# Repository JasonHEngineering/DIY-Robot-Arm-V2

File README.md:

## DIY Robot Arm V2
This repository is for archiving a prior 6 DOF robot project that is no longer maintained.
I am now working on the next V3 version instead. 

### Contents
| Folder  | Contents|
| ------------- | ------------- |
| [Adaptor Board](https://github.com/JasonHEngineering/DIY-Robot-Arm-V2/tree/main/Adaptor%20Board%20(schema%2C%20gerbers%2C%20kicad%20project%20folder)) | KiCad Project files. Gerber files for PCB. But no SMD assembly because for this variant of adaptor board, I did the soldering myself using both soldering iron and hot air solder. |
| [Arduino Nano](https://github.com/JasonHEngineering/DIY-Robot-Arm-V2/tree/main/Arduino%20Nano%20(.ino%20file)) | Load this file into Arduino Nano 33 BLE/IoT device. This is to be mounted into adaptor board above. |
| [CAD files](https://github.com/JasonHEngineering/DIY-Robot-Arm-V2/tree/main/CAD%20files%20(2d%2C%20step)) | Step files and 2d drawings. 2d drawings are not fully detailed; mainly the threads and tight tolerances are detailed. |
| [Raspberry Pi](https://github.com/JasonHEngineering/DIY-Robot-Arm-V2/tree/main/Raspberry%20Pi%20(plotly%20dash%20host)) | Python script and dependencies to be run on raspberry Pi 3/4 |

### Mechanical Structure
Machined CNC parts placement in assembly as shown below. 
> [!NOTE]
> In such a setup, micro limit switches can only zero the respective axis angles approximately. Next version shall use absolute encoders.    

Below illustration of user interface dealing with forward kinematics values:  

### Inverse Kinematics Solver
[Python solver](https://github.com/JasonHEngineering/Inverse-Kinematics)
1. Inverse Kinematics (CCD) – Cyclic Coordinate Descent in 3d space
2. Inverse Kinematics (vector formula Jacobian) - Euler
3. Inverse Kinematics (Numerical Jacobian) - Euler
4. Inverse Kinematics (Numerical Jacobian) - Quaternion

### Quick Illustration at YouTube

### Additional Info at WordPress
For more data/info, please refer to this [WordPress page](https://jashuang1983.wordpress.com/robotics-6-dof-arm-v2/).

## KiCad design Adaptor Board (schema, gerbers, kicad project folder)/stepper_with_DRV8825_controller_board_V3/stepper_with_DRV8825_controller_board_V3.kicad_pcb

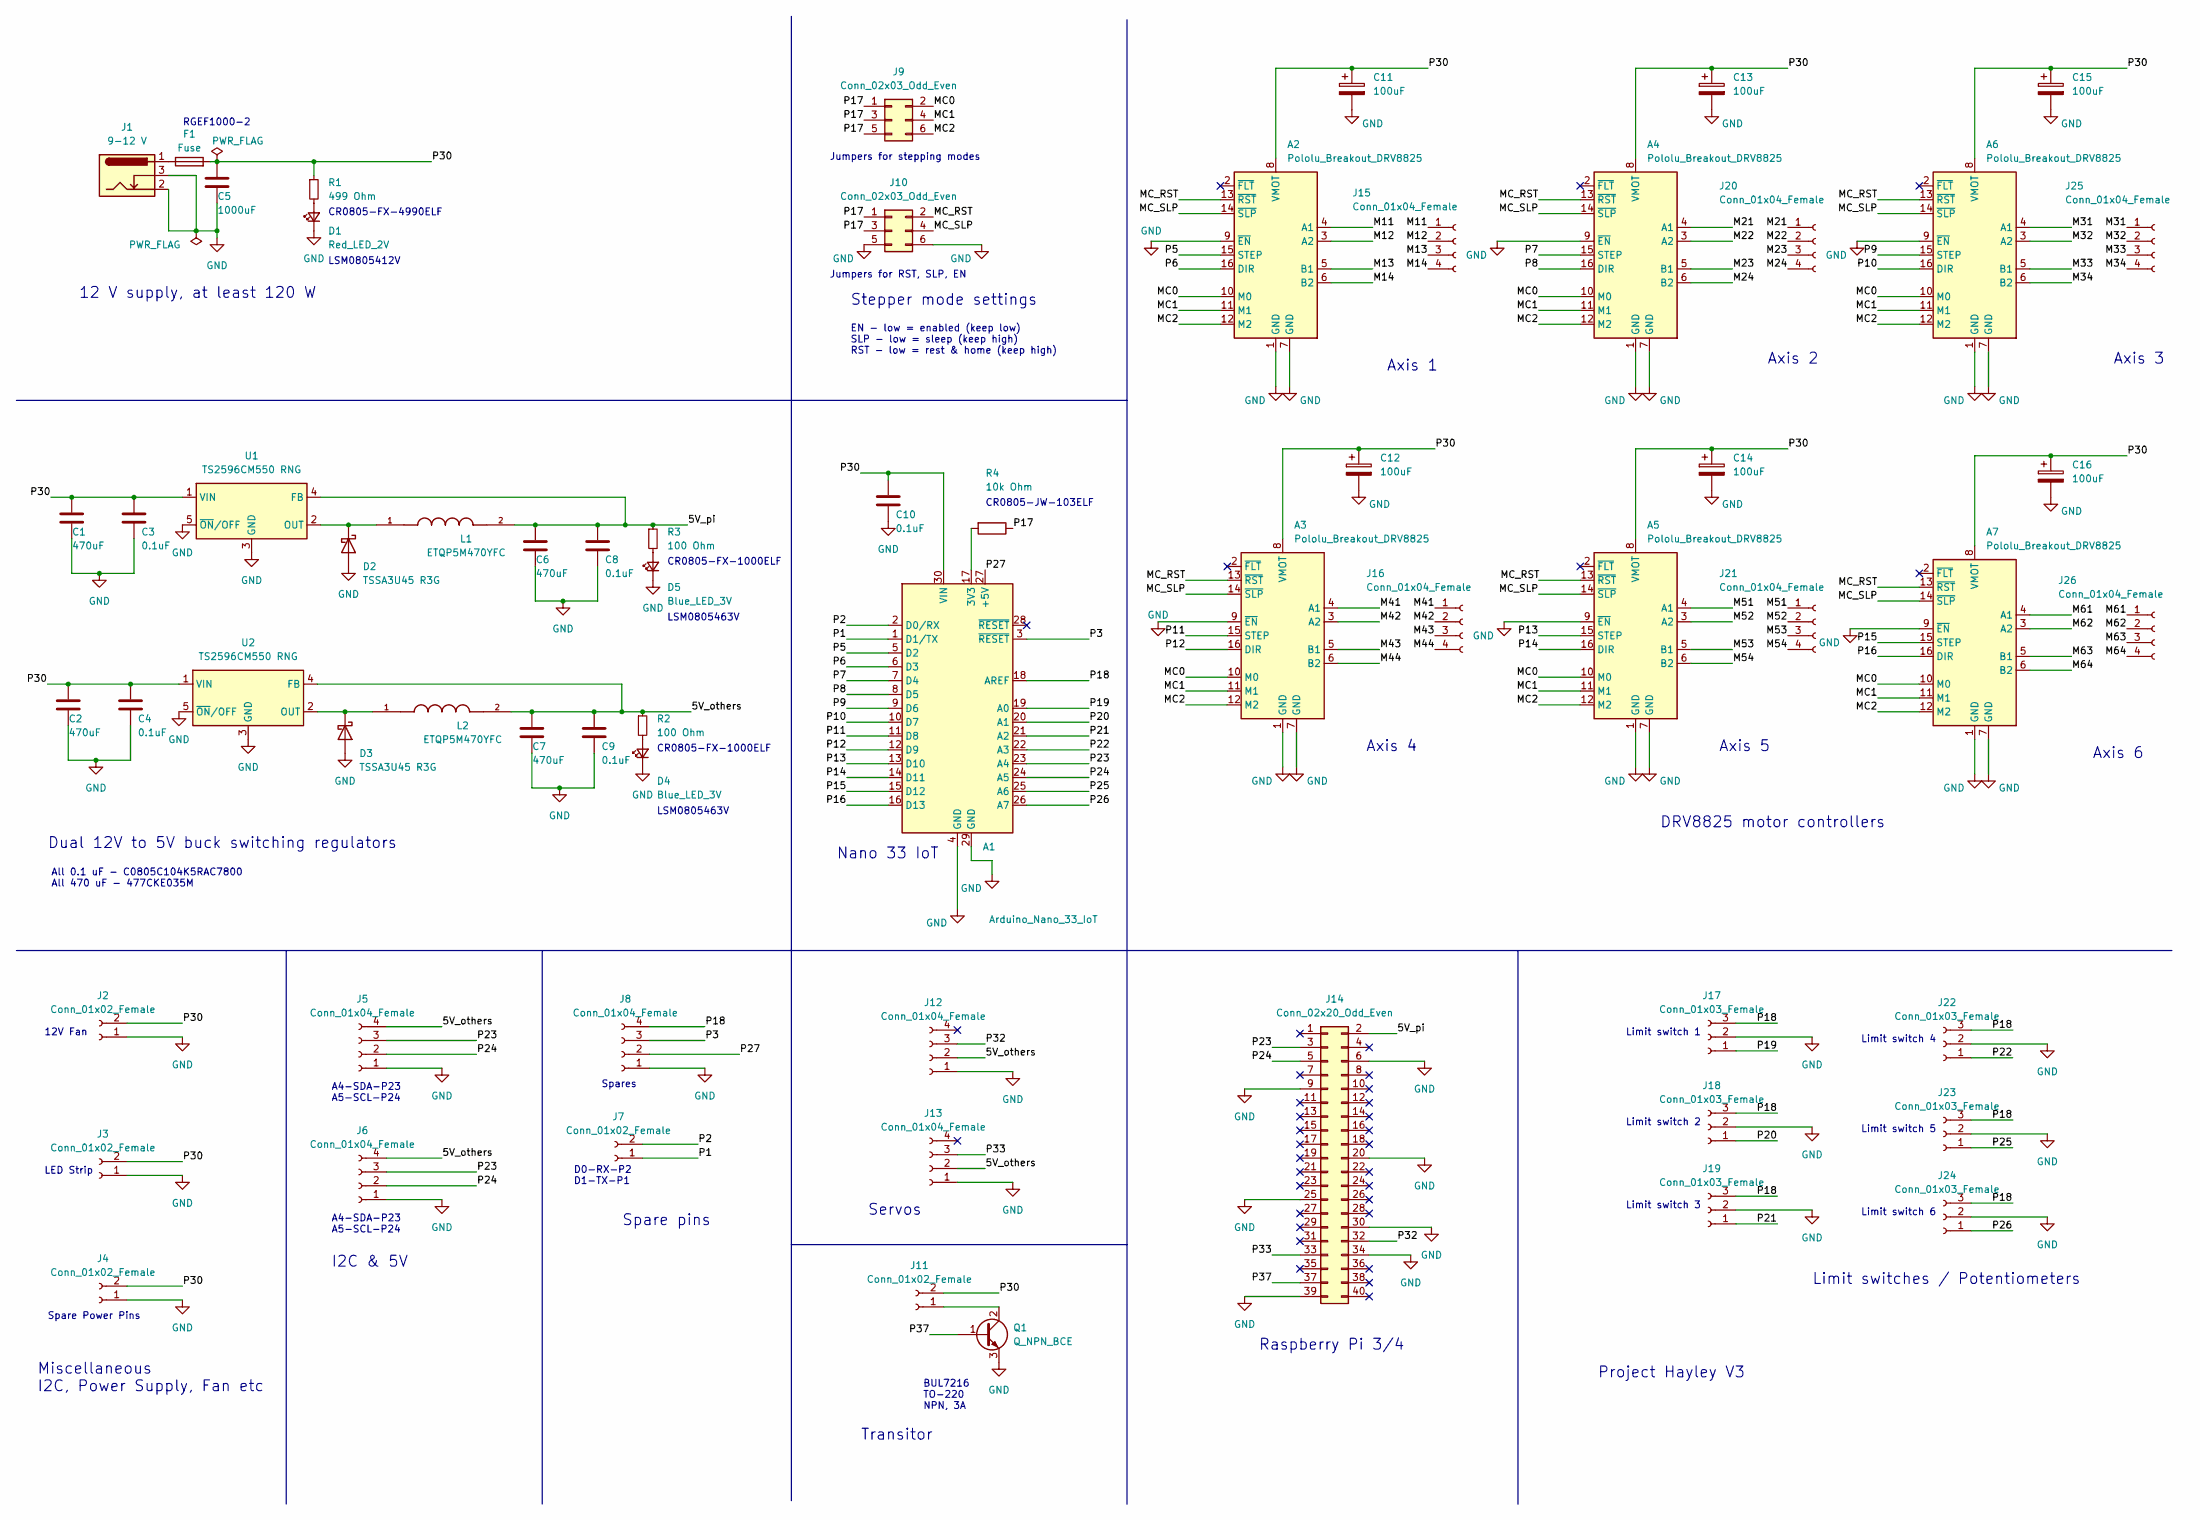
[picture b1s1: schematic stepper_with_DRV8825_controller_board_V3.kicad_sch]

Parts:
A1: Arduino_Nano_33_IoT; Arduino_Nano
A2, A3, A4, A5, A6, A7: Pololu_Breakout_DRV8825; Pololu_Breakout-16_15.2x20.3mm
C1, C2, C6, C7: 470uF; CP_Radial_D10.0mm_P5.00mm
C3, C4, C8, C9, C10: 0.1uF; C_0805_2012Metric_Pad1.18x1.45mm_HandSolder
C5: 1000uF; CP_Radial_D10.0mm_P5.00mm
C11, C12, C13, C14, C15, C16: 100uF; CP_Radial_D5.0mm_P2.50mm
D1: Red_LED_2V; LED_0805_2012Metric_Pad1.15x1.40mm_HandSolder
D2, D3: TSSA3U45 R3G; D_SMA
D4, D5: Blue_LED_3V; LED_0805_2012Metric_Pad1.15x1.40mm_HandSolder
F1: Fuse; FUSRB510W81L1358T310H1980
J1: 9-12 V; NINIGI_DC-005
J2, J3, J4, J7: Conn_01x02_Female; JST_PH_B2B-PH-K_1x02_P2.00mm_Vertical
J5, J6, J8, J12, J13: Conn_01x04_Female; JST_PH_B4B-PH-K_1x04_P2.00mm_Vertical
J9, J10: Conn_02x03_Odd_Even; PinHeader_2x03_P2.54mm_Vertical
J11: Conn_01x02_Female; JST_XH_B2B-XH-A_1x02_P2.50mm_Vertical
J14: Conn_02x20_Odd_Even; PinHeader_2x20_P2.54mm_Vertical
J15, J16, J20, J21, J25, J26: Conn_01x04_Female; JST_XH_B4B-XH-A_1x04_P2.50mm_Vertical
J17, J18, J19, J22, J23, J24: Conn_01x03_Female; JST_PH_B3B-PH-K_1x03_P2.00mm_Vertical
L1, L2: ETQP5M470YFC; IND_ETQP5M470YFC; PARTREV 1-Feb-20
Q1: Q_NPN_BCE; TO-220-3_Vertical
R1: 499 Ohm; R_0805_2012Metric_Pad1.20x1.40mm_HandSolder
R2, R3: 100 Ohm; R_0805_2012Metric_Pad1.20x1.40mm_HandSolder
R4: 10k Ohm; R_0805_2012Metric_Pad1.20x1.40mm_HandSolder
U1, U2: TS2596CM550 RNG; TO-263-5_TabPin3

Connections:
/5V_others: C7.1, C9.1, J5.4, J6.4, J12.2, J13.2, L2.2, R2.1, U2.4 (FB)
/5V_pi: C6.1, C8.1, J14.2, L1.2, R3.1, U1.4 (FB)
/M11: A2.4 (A1), J15.1
/M12: A2.3 (A2), J15.2
/M13: A2.5 (B1), J15.3
/M14: A2.6 (B2), J15.4
/M21: A4.4 (A1), J20.1
/M22: A4.3 (A2), J20.2
/M23: A4.5 (B1), J20.3
/M24: A4.6 (B2), J20.4
/M31: A6.4 (A1), J25.1
/M32: A6.3 (A2), J25.2
/M33: A6.5 (B1), J25.3
/M34: A6.6 (B2), J25.4
/M41: A3.4 (A1), J16.1
/M42: A3.3 (A2), J16.2
/M43: A3.5 (B1), J16.3
/M44: A3.6 (B2), J16.4
/M51: A5.4 (A1), J21.1
/M52: A5.3 (A2), J21.2
/M53: A5.5 (B1), J21.3
/M54: A5.6 (B2), J21.4
/M61: A7.4 (A1), J26.1
/M62: A7.3 (A2), J26.2
/M63: A7.5 (B1), J26.3
/M64: A7.6 (B2), J26.4
/MC0: A2.10 (M0), A3.10 (M0), A4.10 (M0), A5.10 (M0), A6.10 (M0), A7.10 (M0), J9.2
/MC1: A2.11 (M1), A3.11 (M1), A4.11 (M1), A5.11 (M1), A6.11 (M1), A7.11 (M1), J9.4
/MC2: A2.12 (M2), A3.12 (M2), A4.12 (M2), A5.12 (M2), A6.12 (M2), A7.12 (M2), J9.6
/MC_RST: A2.13 (~RST), A3.13 (~RST), A4.13 (~RST), A5.13 (~RST), A6.13 (~RST), A7.13 (~RST), J10.2
/MC_SLP: A2.14 (~SLP), A3.14 (~SLP), A4.14 (~SLP), A5.14 (~SLP), A6.14 (~SLP), A7.14 (~SLP), J10.4
/P1: A1.1 (D1/TX), J7.1
/P2: A1.2 (D0/RX), J7.2
/P3: A1.3 (~RESET), J8.3
/P5: A1.5 (D2), A2.15 (STEP)
/P6: A1.6 (D3), A2.16 (DIR)
/P7: A1.7 (D4), A4.15 (STEP)
/P8: A1.8 (D5), A4.16 (DIR)
/P9: A1.9 (D6), A6.15 (STEP)
/P10: A1.10 (D7), A6.16 (DIR)
/P11: A1.11 (D8), A3.15 (STEP)
/P12: A1.12 (D9), A3.16 (DIR)
/P13: A1.13 (D10), A5.15 (STEP)
/P14: A1.14 (D11), A5.16 (DIR)
/P15: A1.15 (D12), A7.15 (STEP)
/P16: A1.16 (D13), A7.16 (DIR)
/P17: J9.1, J9.3, J9.5, J10.1, J10.3, R4.1
/P18: A1.18 (AREF), J8.4, J17.3, J18.3, J19.3, J22.3, J23.3, J24.3
/P19: A1.19 (A0), J17.1
/P20: A1.20 (A1), J18.1
/P21: A1.21 (A2), J19.1
/P22: A1.22 (A3), J22.1
/P23: A1.23 (A4), J5.3, J6.3, J14.3
/P24: A1.24 (A5), J5.2, J6.2, J14.5
/P25: A1.25 (A6), J23.1
/P26: A1.26 (A7), J24.1
/P27: A1.27 (+5V), J8.2
/P30: A1.30 (VIN), A2.8 (VMOT), A3.8 (VMOT), A4.8 (VMOT), A5.8 (VMOT), A6.8 (VMOT), A7.8 (VMOT), C1.1, C2.1, C3.1, C4.1, C5.1, C10.1, C11.1, C12.1, C13.1, C14.1, C15.1, C16.1, F1.2, J2.2, J3.2, J4.2, J11.2, R1.1, U1.1 (VIN), U2.1 (VIN)
/P32: J12.3, J14.32
/P33: J13.3, J14.33
/P37: J14.37, Q1.1 (B)
GND: A1.4 (GND), A1.29 (GND), A2.1 (GND), A2.7 (GND), A2.9 (~EN), A3.1 (GND), A3.7 (GND), A3.9 (~EN), A4.1 (GND), A4.7 (GND), A4.9 (~EN), A5.1 (GND), A5.7 (GND), A5.9 (~EN), A6.1 (GND), A6.7 (GND), A6.9 (~EN), A7.1 (GND), A7.7 (GND), A7.9 (~EN), C1.2, C2.2, C3.2, C4.2, C5.2, C6.2, C7.2, C8.2, C9.2, C10.2, C11.2, C12.2, C13.2, C14.2, C15.2, C16.2, D1.1 (K), D2.2 (A), D3.2 (A), D4.1 (K), D5.1 (K), J1.2, J1.3, J2.1, J3.1, J4.1, J5.1, J6.1, J8.1, J10.5, J10.6, J12.1, J13.1, J14.6, J14.9, J14.20, J14.25, J14.30, J14.34, J14.39, J17.2, J18.2, J19.2, J22.2, J23.2, J24.2, Q1.3 (E), U1.3 (GND), U1.5 (~ON/OFF), U2.3 (GND), U2.5 (~ON/OFF)
unnamed: A1.17 (3V3), R4.2
unnamed: D1.2 (A), R1.2
unnamed: D2.1 (K), L1.1, U1.2 (OUT)
unnamed: D3.1 (K), L2.1, U2.2 (OUT)
unnamed: D4.2 (A), R2.2
unnamed: D5.2 (A), R3.2
unnamed: F1.1, J1.1
unnamed: J11.1, Q1.2 (C)

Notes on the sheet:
A4-SDA-P23 A5-SCL-P24
Limit switch 2
Jumpers for stepping modes
Project Hayley V3
Limit switches / Potentiometers
Miscellaneous I2C, Power Supply, Fan etc
CR0805-JW-103ELF
D0-RX-P2 D1-TX-P1
All 0.1 uF - C0805C104K5RAC7800 All 470 uF - 477CKE035M
CR0805-FX-1000ELF
Axis 4
BUL7216 TO-220 NPN, 3A
Axis 1
Limit switch 1
Limit switch 6
CR0805-FX-4990ELF
Limit switch 4
Servos
Limit switch 5
LSM0805463V
Stepper mode settings
EN - low = enabled (keep low) SLP - low = sleep (keep high) RST - low = rest & home (keep high)
Axis 6
Transitor
LSM0805412V
LED Strip
RGEF1000-2
Spare Power Pins
Spares
I2C & 5V
Limit switch 3
Axis 2
12V Fan
Spare pins
Nano 33 IoT
Dual 12V to 5V buck switching regulators
Jumpers for RST, SLP, EN
Axis 5
Axis 3
12 V supply, at least 120 W

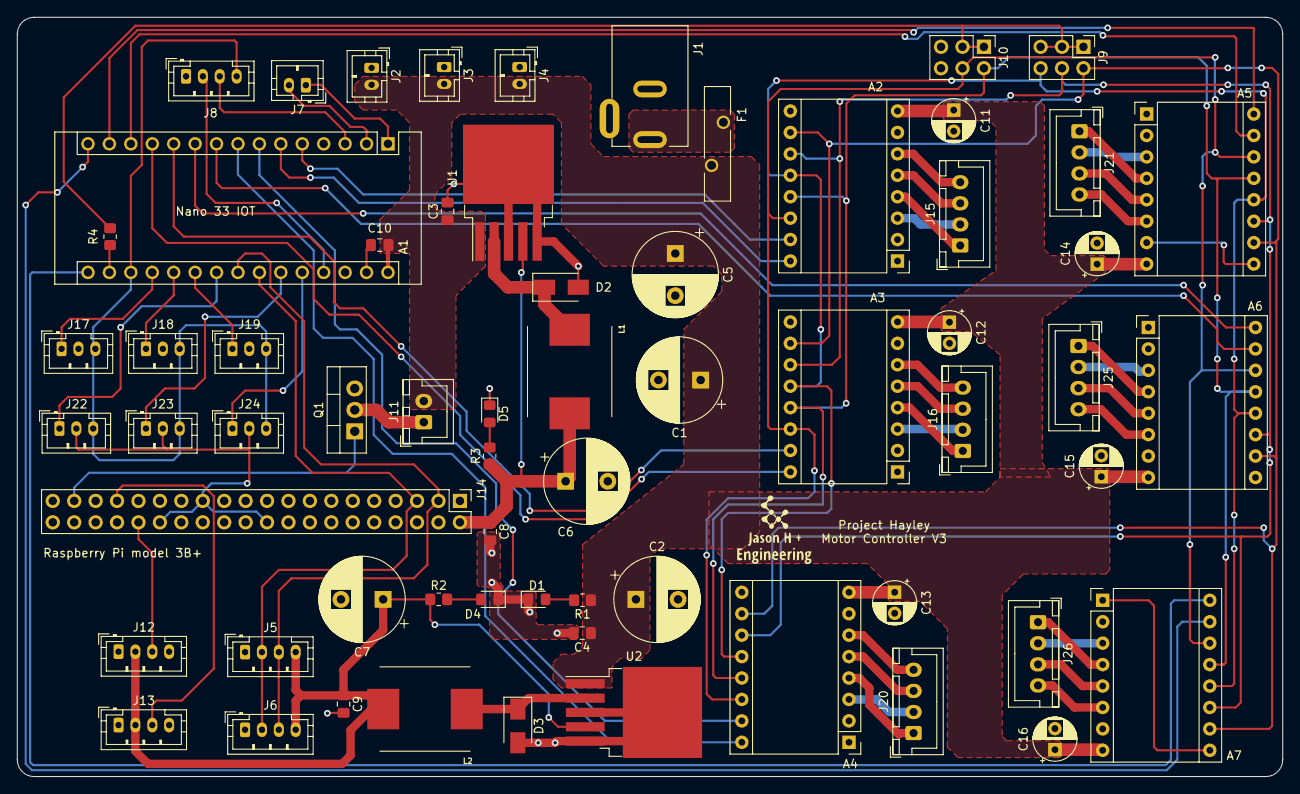
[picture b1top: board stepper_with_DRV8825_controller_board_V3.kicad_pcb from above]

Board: 2 copper layers, 150.0 x 90.0 mm, 64 parts (0 on the bottom side), 70 nets.

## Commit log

2024-09-14 Initial Upload
    Partial upload only - appending more files
2024-09-15 Second upload for python and .ino files
    "Raspberry Pi (plotly dash host)" to be copied to raspberry Pi 3/4 and run "IK_user_interface_V39.py"
    "Project_Hayley_V15_10May24" to be run on a Arduino nano 33 IoT/BLE, which is in turn mounted on adaptor board - see schematics "Adaptor Board (schema, gerbers, kicad project folder)"
2024-09-15 Upload images
    Upload images as illustrations for readme
2024-09-15 Create README.md
    Initial README.md creation
2024-09-15 Update README.md
    Update for illustration with more media files
2024-09-15 Update README.md
    Added table to explain contents. Added placeholder for inverse kinematics solver.
2024-09-19 Update README.md
    Updated link for IK solver
